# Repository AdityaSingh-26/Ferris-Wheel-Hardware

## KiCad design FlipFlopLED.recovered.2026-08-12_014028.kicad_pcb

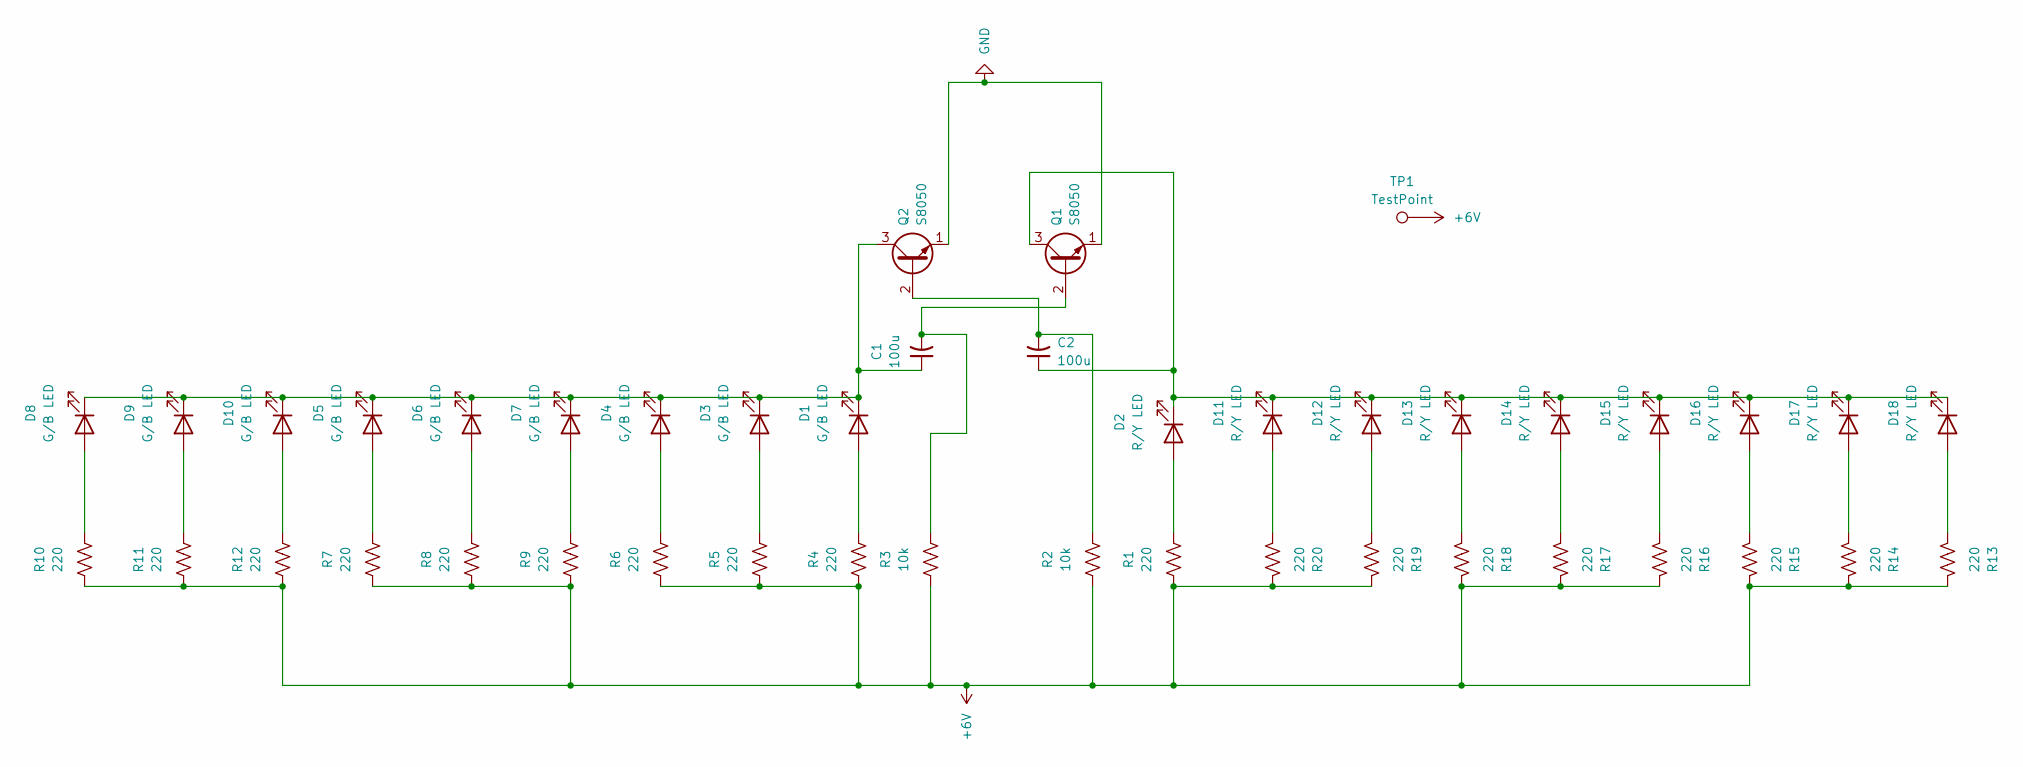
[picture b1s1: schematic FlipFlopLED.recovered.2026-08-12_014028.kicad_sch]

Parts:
C1, C2: 100u; CP_Radial_D6.3mm_P2.50mm
D1, D3, D4, D5, D6, D7, D8, D9, D10: G/B LED; LED_D5.0mm
D2, D11, D12, D13, D14, D15, D16, D17, D18: R/Y LED; LED_D5.0mm
Q1, Q2: S8050; TO-92_Inline
R1, R4, R5, R6, R7, R8, R9, R10, R11, R12, R13, R14, R15, R16, R17, R18, R19, R20: 220; R_Axial_DIN0207_L6.3mm_D2.5mm_P7.62mm_Horizontal
R2, R3: 10k; R_Axial_DIN0207_L6.3mm_D2.5mm_P7.62mm_Horizontal
TP1: TestPoint; TestPoint_THTPad_D2.0mm_Drill1.0mm

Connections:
+6V: R1.1, R2.1, R3.1, R4.1, R5.1, R6.1, R7.1, R8.1, R9.1, R10.1, R11.1, R12.1, R13.1, R14.1, R15.1, R16.1, R17.1, R18.1, R19.1, R20.1, TP1.1 (1_1)
GND: Q1.1 (E), Q2.1 (E)
unnamed: D1.2 (A), R4.2
unnamed: C1.1, D1.1 (K), D3.1 (K), D4.1 (K), D5.1 (K), D6.1 (K), D7.1 (K), D8.1 (K), D9.1 (K), D10.1 (K), Q2.3 (C)
unnamed: D2.2 (A), R1.2
unnamed: D3.2 (A), R5.2
unnamed: D4.2 (A), R6.2
unnamed: D5.2 (A), R7.2
unnamed: D6.2 (A), R8.2
unnamed: D7.2 (A), R9.2
unnamed: D8.2 (A), R10.2
unnamed: D9.2 (A), R11.2
unnamed: D10.2 (A), R12.2
unnamed: D11.2 (A), R20.2
unnamed: C2.1, D2.1 (K), D11.1 (K), D12.1 (K), D13.1 (K), D14.1 (K), D15.1 (K), D16.1 (K), D17.1 (K), D18.1 (K), Q1.3 (C)
unnamed: D12.2 (A), R19.2
unnamed: D13.2 (A), R18.2
unnamed: D14.2 (A), R17.2
unnamed: D15.2 (A), R16.2
unnamed: D16.2 (A), R15.2
unnamed: D17.2 (A), R14.2
unnamed: D18.2 (A), R13.2
unnamed: C1.2, Q1.2 (B), R3.2
unnamed: C2.2, Q2.2 (B), R2.2

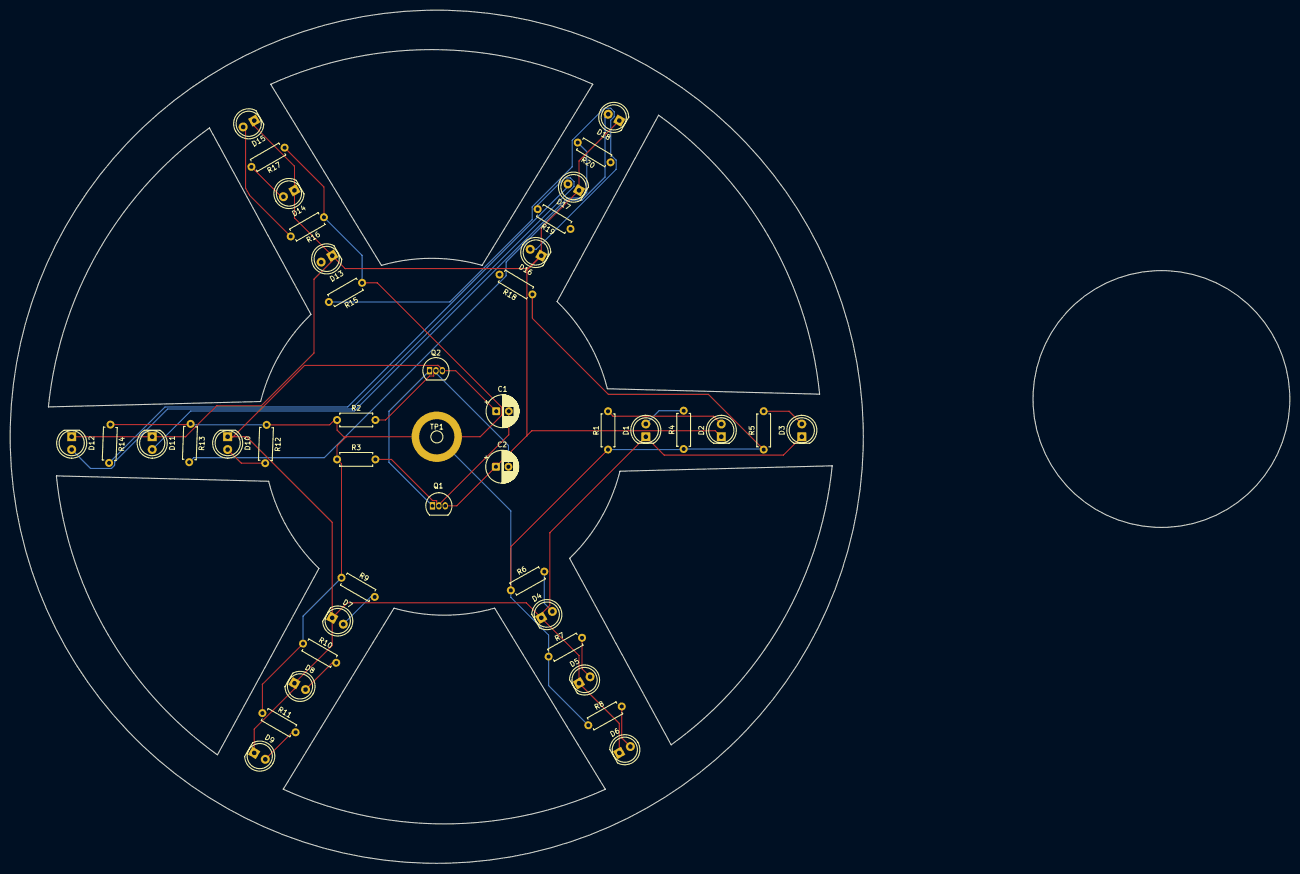
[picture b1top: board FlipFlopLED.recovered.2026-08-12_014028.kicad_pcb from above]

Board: 2 copper layers, 169.5 x 169.5 mm, 43 parts (0 on the bottom side), 24 nets.
